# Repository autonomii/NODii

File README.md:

This repository contains code, board files and more for Autonomii's NODii products.  We spend a great deal of time working out the details and Open Source our projects. So please pay it forward and we hope you consider purchasing from us on your projects.

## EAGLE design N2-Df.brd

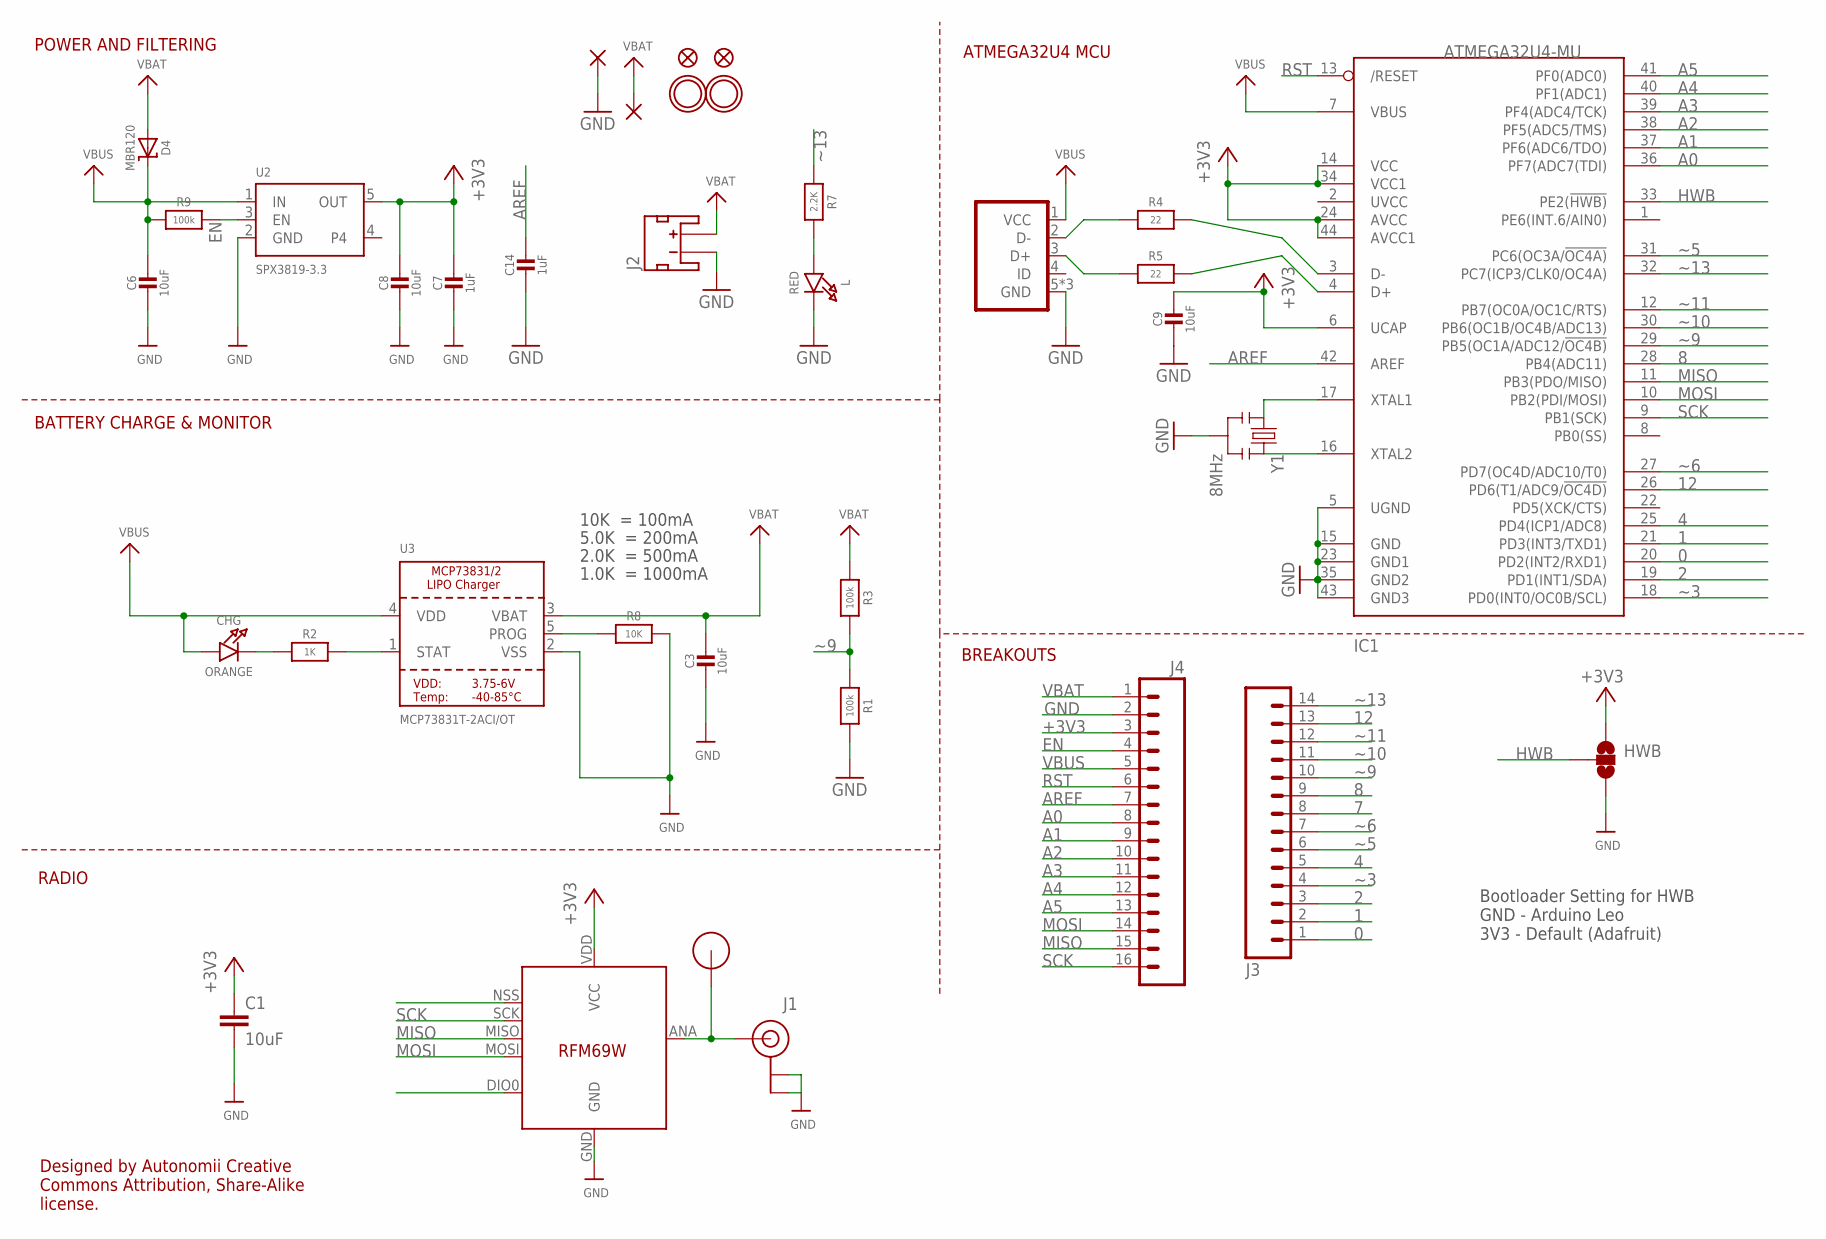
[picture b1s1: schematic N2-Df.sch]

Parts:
C1: 10uF; 0603-CAP
C3, C6, C8, C9: 10uF; 0805-NO
C7, C14: 1uF; 0603-NO
CHG: ORANGE; CHIPLED_0805_NOOUTLINE
D4: MBR120; SOD-123
HWB: SOLDERJUMPER_2WAYPASTE1&2; SJ_3_PASTE1&2
IC1: ATMEGA32U4-MU; TQFN44_7MM
J1: U.FL
J2: JST_2MM_MALE; JST-2-SMD
J3: M14STACKING_BIG; 1X14_STACKING_BIG
J4: M16STACKING_BIG; 1X16_STACKING_BIG
L: RED; CHIPLED_0805_NOOUTLINE
PAD1, PAD2: 1,6/0,9
R1, R3, R9: 100k; 0603-NO
R2: 1K; 0603-NO
R4, R5: 22; 0603-NO
R7: 2.2K; 0603-NO
R8: 10K; 0603-NO
U2: SPX3819-3.3; SOT23-5
U3: MCP73831T-2ACI/OT; SOT23-5
U$7: RFM12B_ANTENNA; RFM12B-ANTENNA
U$10: RFM69; RFM69W-MINPADS
U$31, U$32: MOUNTINGHOLE2.5; MOUNTINGHOLE_2.5_PLATED
U$34, U$35: FIDUCIAL""; FIDUCIAL_1MM
USB: USB-RECEPTABLE; FCI-10103594-0001LF
Y1: 8MHz; RESONATOR-SMD

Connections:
0: IC1.20 (PD2(INT2/RXD1)), J3.1
1: IC1.21 (PD3(INT3/TXD1)), J3.2
2: IC1.19 (PD1(INT1/SDA)), J3.3
4: IC1.25 (PD4(ICP1/ADC8)), J3.5
7: J3.8, U$10.DIO0
8: IC1.28 (PB4(ADC11)), J3.9
12: IC1.26 (PD6(T1/ADC9/!OC4D)), J3.13
+3V3: C1.1, C7.1, C8.1, C9.1, HWB.1, IC1.6 (UCAP), IC1.14 (VCC), IC1.24 (AVCC), IC1.34 (VCC1), IC1.44 (AVCC1), J4.3, U2.5 (OUT), U$10.VDD (VCC)
A0: IC1.36 (PF7(ADC7(TDI)), J4.8
A1: IC1.37 (PF6(ADC6/TDO)), J4.9
A2: IC1.38 (PF5(ADC5/TMS)), J4.10
A3: IC1.39 (PF4(ADC4/TCK)), J4.11
A4: IC1.40 (PF1(ADC1)), J4.12
A5: IC1.41 (PF0(ADC0)), J4.13
ANT: J1.P$3 (SIGNAL), U$7.P$1, U$10.ANA (ANT)
AREF: C14.1, IC1.42 (AREF), J4.7
D+: IC1.4 (D+), R5.2
D++: R5.1, USB.3 (D+)
D-: IC1.3 (D-), R4.2
D--: R4.1, USB.2 (D-)
EN: J4.4, R9.2, U2.3 (EN)
GND: C1.2, C3.2, C6.2, C7.2, C8.2, C9.2, C14.2, HWB.3, IC1.5 (UGND), IC1.15 (GND), IC1.23 (GND1), IC1.35 (GND2), IC1.43 (GND3), J1.P$1 (GND), J1.P$2 (GND), J2.1 (-), J4.2, L.C, PAD2.1, R1.2, R8.2, U2.2 (GND), U3.2 (VSS), U$10.GND, USB.5 (GND), USB.P$3 (GND), USB.P$4 (GND), Y1.2
HWB: HWB.2, IC1.33 (PE2(!HWB))
MISO: IC1.11 (PB3(PDO/MISO)), J4.15, U$10.MISO
MOSI: IC1.10 (PB2(PDI/MOSI)), J4.14, U$10.MOSI
unnamed: CHG.C, R2.1
unnamed: L.A, R7.2
unnamed: R2.2, U3.1 (STAT)
unnamed: R8.1, U3.5 (PROG)
unnamed: IC1.16 (XTAL2), Y1.3
unnamed: IC1.17 (XTAL1), Y1.1
RST: IC1.13 (/RESET), J4.6
SCK: IC1.9 (PB1(SCK)), J4.16, U$10.SCK
SS: U$10.NSS (SEL)
VBAT: C3.1, D4.A, J2.2 (+), J4.1, PAD1.1, R3.1, U3.3 (VBAT)
VBUS: C6.1, CHG.A, D4.C, IC1.7 (VBUS), J4.5, R9.1, U2.1 (IN), U3.4 (VDD), USB.1 (VCC)
~3: IC1.18 (PD0(INT0/OC0B/SCL)), J3.4
~5: IC1.31 (PC6(OC3A/!OC4A)), J3.6
~6: IC1.27 (PD7(OC4D/ADC10/T0)), J3.7
~9: IC1.29 (PB5(OC1A/ADC12/!OC4B)), J3.10, R1.1, R3.2
~10: IC1.30 (PB6(OC1B/OC4B/ADC13)), J3.11
~11: IC1.12 (PB7(OC0A/OC1C/RTS)), J3.12
~13: IC1.32 (PC7(ICP3/CLK0/OC4A)), J3.14, R7.1

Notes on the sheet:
POWER AND FILTERING
ATMEGA32U4 MCU
10K = 100mA
5.0K = 200mA
2.0K = 500mA
1.0K = 1000mA
BATTERY CHARGE & MONITOR
BREAKOUTS
RADIO
Bootloader Setting for HWB GND - Arduino Leo 3V3 - Default (Adafruit)
Designed by Autonomii Creative Commons Attribution, Share-Alike license.

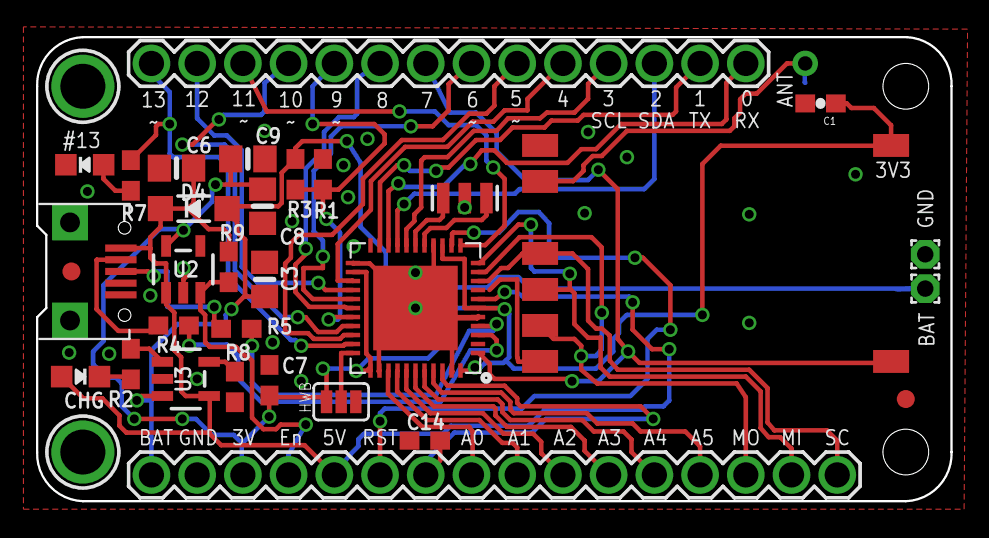
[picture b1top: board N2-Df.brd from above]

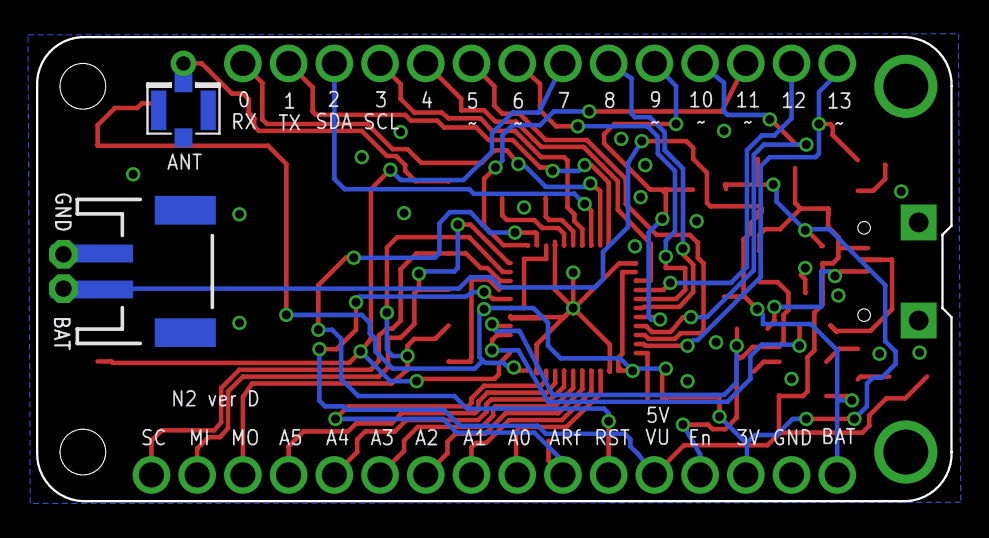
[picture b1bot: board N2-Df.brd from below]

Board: 2 copper layers, 50.8 x 25.8 mm, 36 parts (2 on the bottom side), 42 nets.

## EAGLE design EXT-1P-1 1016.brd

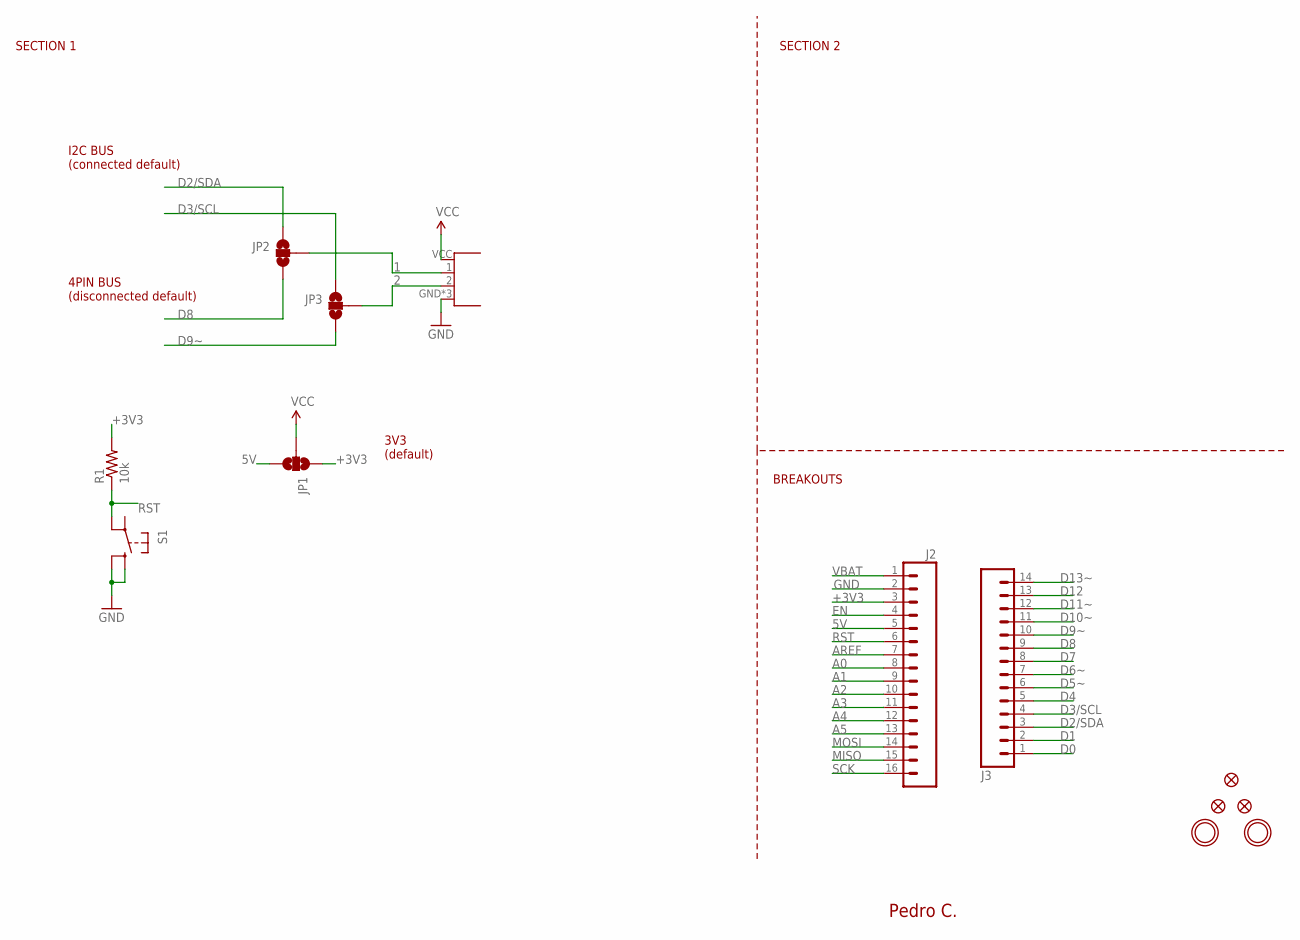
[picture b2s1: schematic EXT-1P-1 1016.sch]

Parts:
FD1, FD2, FD3: FIDUCIALUFIDUCIAL; MICRO-FIDUCIAL
J1: USB-A-RECP-SINGLE-SMD; USB-A-RECP-GNC-SMD
J2: M16PTH; 1X16
J3: M14; 1X14
JP1, JP2, JP3: SOLDERJUMPER_2WAYPASTE1&2; SJ_3_PASTE1&2
MP1, MP2: MOUNTINGHOLE2.5_THICK; MOUNTINGHOLE_2.5_PLATED_THICK
R1: 10k; 0603-RES
S1: TACT-SWITCH

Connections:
1: J1.1, JP2.2
2: J1.2, JP3.2
5V: J2.5, JP1.3
+3V3: J2.3, JP1.1, R1.2
A0: J2.8
A1: J2.9
A2: J2.10
A3: J2.11
A4: J2.12
A5: J2.13
AREF: J2.7
D0: J3.1
D1: J3.2
D2/SDA: J3.3, JP2.1
D3/SCL: J3.4, JP3.1
D4: J3.5
D5~: J3.6
D6~: J3.7
D7: J3.8
D8: J3.9, JP2.3
D9~: J3.10, JP3.3
D10~: J3.11
D11~: J3.12
D12: J3.13
D13~: J3.14
EN: J2.4
GND: J1.GND, J1.GND1 (GND), J1.GND2 (GND), J2.2, S1.3, S1.4
MISO: J2.15
MOSI: J2.14
RST: J2.6, R1.1, S1.2
SCK: J2.16
VBAT: J2.1
VCC: J1.VCC, JP1.2

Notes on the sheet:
SECTION 1
SECTION 2
BREAKOUTS
I2C BUS (connected default)
4PIN BUS (disconnected default)
3V3 (default)
Pedro C.

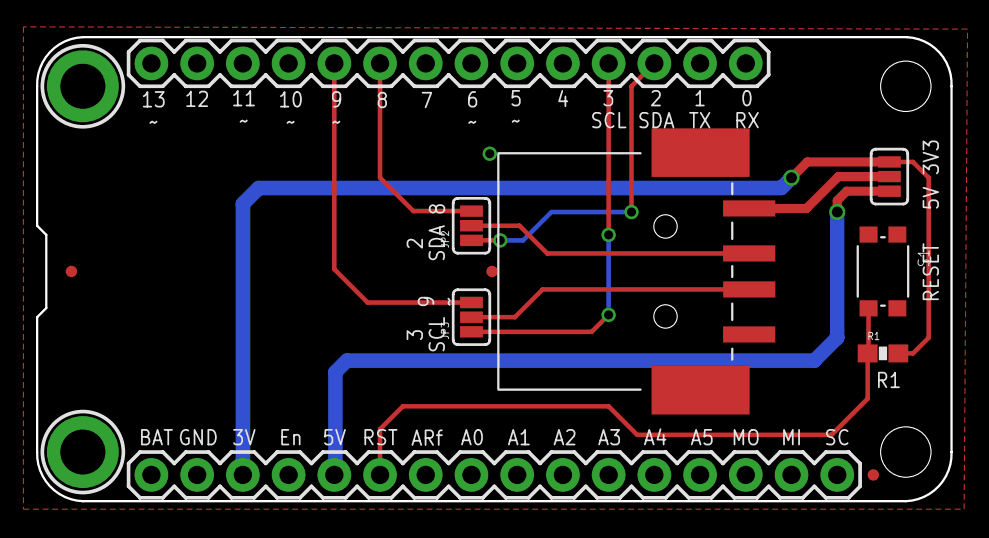
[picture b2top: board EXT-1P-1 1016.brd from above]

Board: 2 copper layers, 50.8 x 25.8 mm, 13 parts (0 on the bottom side), 11 nets.

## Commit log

2016-11-02 Uploaded Extender board.
2016-11-03 board file
2016-11-03 Upload NODii 2D Eagle Files
2016-11-03 Upload N2-D board files.
2016-11-04 Create LICENSE
2016-11-20 Arduino Board Manager Files

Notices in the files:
parts and their libraries:
SparkFun-Aesthetics: Licensing: Creative Commons ShareAlike 4.0 International - https://creativecommons.org/licenses/by-sa/4.0
microbuilder: This work is placed in the public domain, and may be freely used for commercial and non-commercial work with the following conditions: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
